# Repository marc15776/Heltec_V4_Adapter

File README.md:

# Heltec LoRa V4 Adapter

This is a fork from [kiu/lofence](https://github.com/kiu/lofence)

I used the the resistor and opamp concept to use  with the [Heltec LoRa V4](https://heltec.org/project/wifi-lora-32-v4/) adc input.
I dont need the microcontroller, LoRa chipset and battery management since that is already integrated on the Heltec V4 board.
I will probably use this in point to point mode with another Heltec board.

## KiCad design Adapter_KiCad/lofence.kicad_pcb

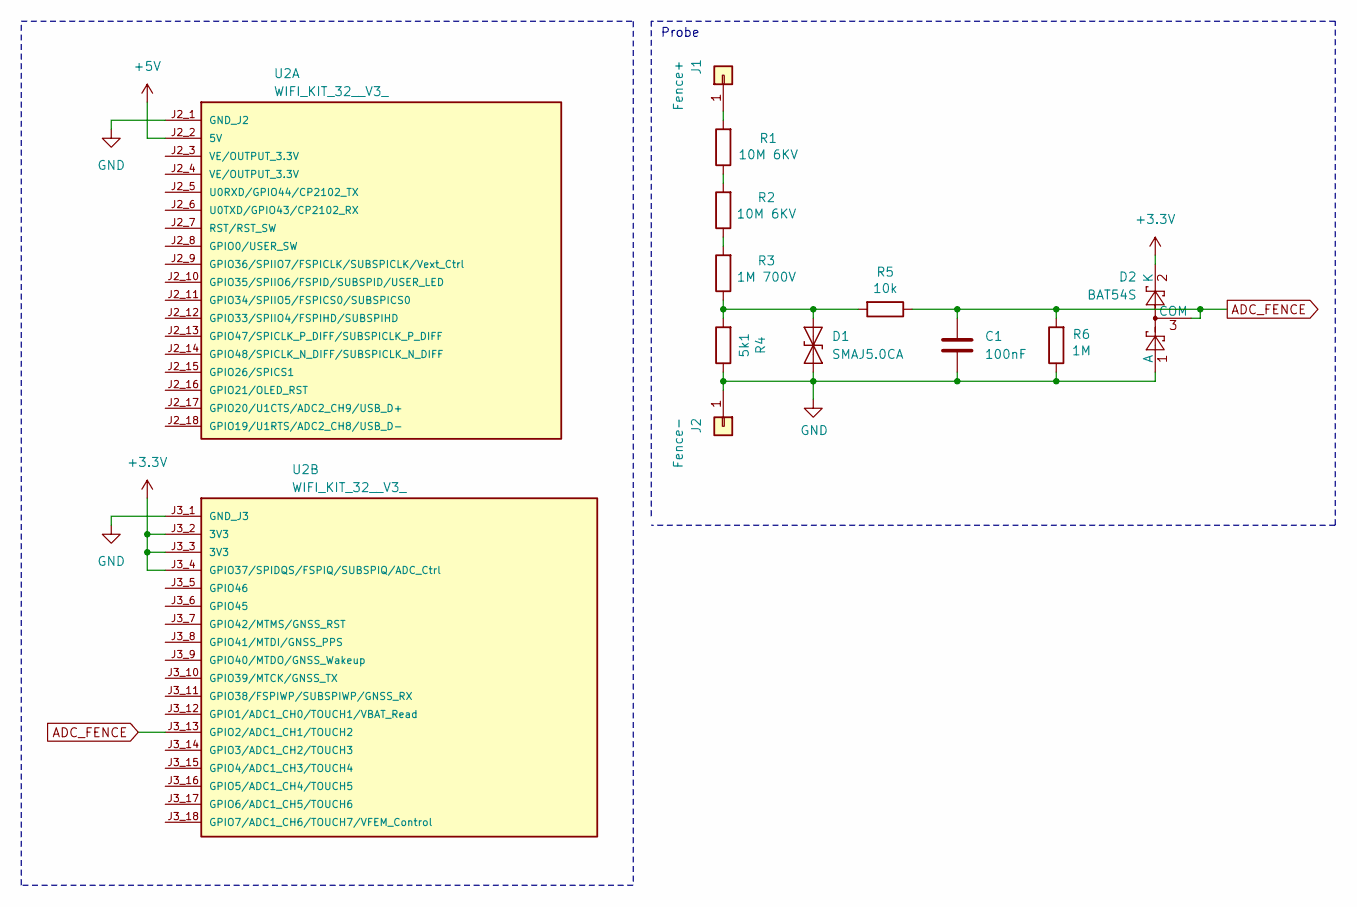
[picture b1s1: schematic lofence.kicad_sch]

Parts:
C1: 100nF; C_0805_2012Metric_Pad1.18x1.45mm_HandSolder
D1: SMAJ5.0CA; D_SMA
D2: BAT54S; SOT-23
J1: Fence+; Measurement_Point_Square-SMD-Pad_Big
J2: Fence-; Measurement_Point_Square-SMD-Pad_Big
R1, R2: 10M 6KV; R_Axial_DIN0414_L11.9mm_D4.5mm_P15.24mm_Horizontal
R3: 1M 700V; R_1206_3216Metric_Pad1.30x1.75mm_HandSolder
R4: 5k1; R_0805_2012Metric_Pad1.20x1.40mm_HandSolder
R5: 10k; R_0805_2012Metric_Pad1.20x1.40mm_HandSolder
R6: 1M; R_0805_2012Metric_Pad1.20x1.40mm_HandSolder
U2: WIFI_KIT_32__V3_; MODULE_WIFI_KIT_32__V3_; PARTREV Rev 1.1

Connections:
+3.3V: D2.2 (K), U2.J3_2 (3V3), U2.J3_3 (3V3), U2.J3_4 (GPIO37/SPIDQS/FSPIQ/SUBSPIQ/ADC_Ctrl)
+5V: U2.J2_2 (5V)
ADC_FENCE: C1.1, D2.3 (COM), R5.1, R6.2, U2.J3_13 (GPIO2/ADC1_CH1/TOUCH2)
GND: C1.2, D1.1 (A1), D2.1 (A), J2.1, R4.1, R6.1, U2.J2_1 (GND_J2), U2.J3_1 (GND_J3)
unnamed: D1.2 (A2), R3.1, R4.2, R5.2
unnamed: J1.1, R1.2
unnamed: R1.1, R2.2
unnamed: R2.1, R3.2

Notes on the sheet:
Probe

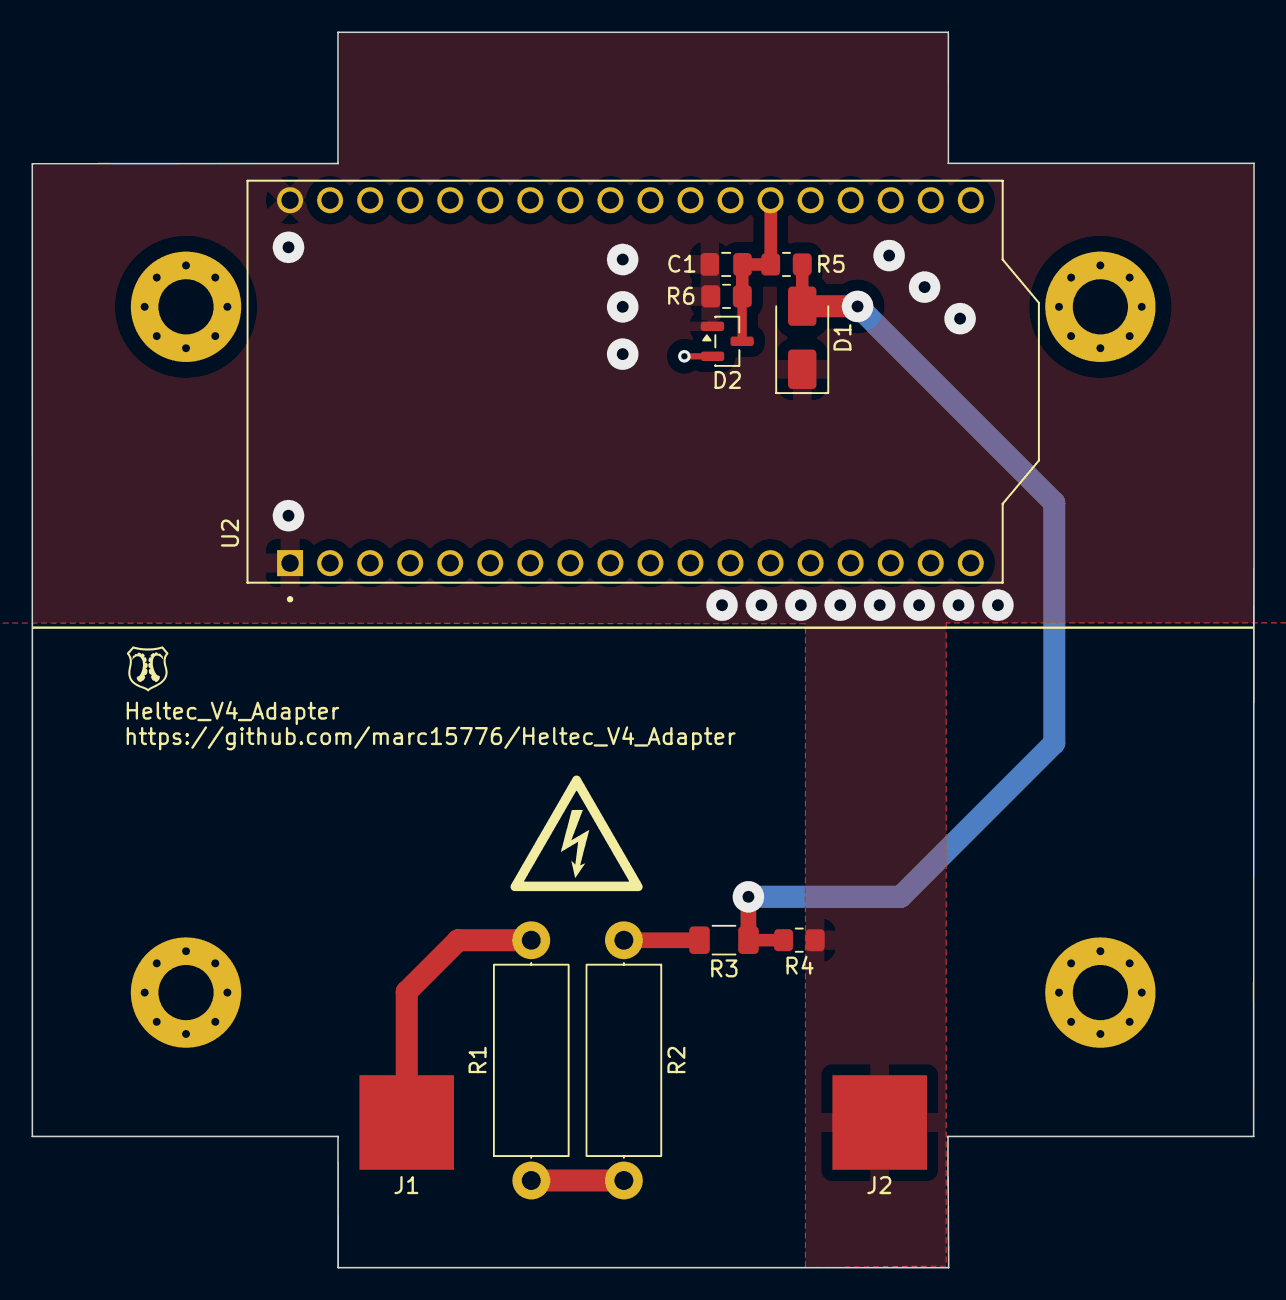
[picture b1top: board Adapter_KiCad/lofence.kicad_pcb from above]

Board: 4 copper layers, 77.5 x 78.4 mm, 12 parts (0 on the bottom side), 7 nets.

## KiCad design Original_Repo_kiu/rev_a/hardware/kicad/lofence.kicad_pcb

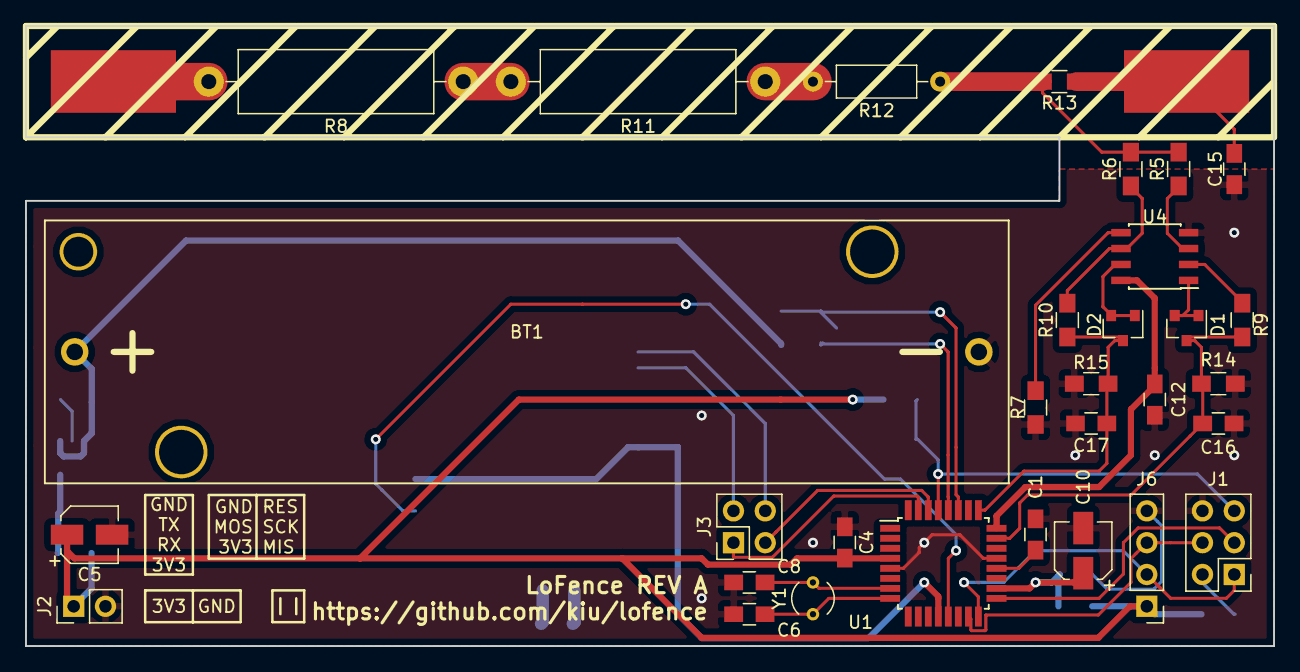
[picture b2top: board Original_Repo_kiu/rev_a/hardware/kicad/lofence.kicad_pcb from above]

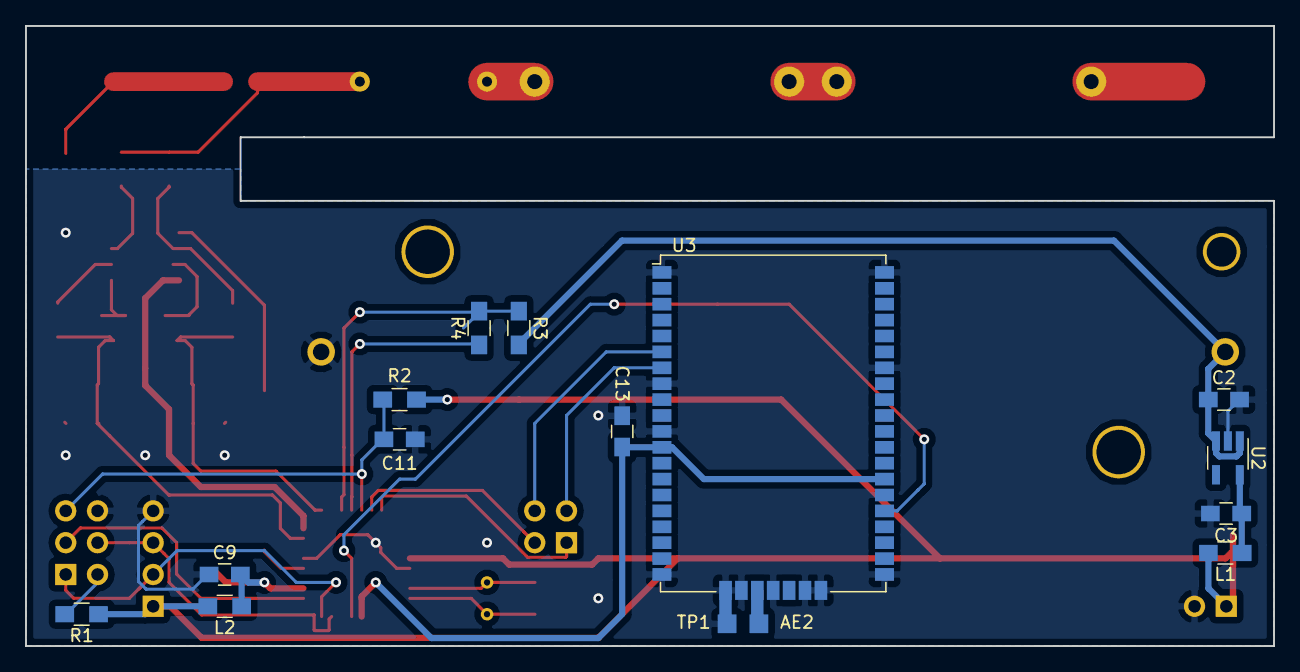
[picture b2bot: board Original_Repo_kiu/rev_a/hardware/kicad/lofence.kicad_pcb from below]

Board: 2 copper layers, 99.7 x 49.5 mm, 48 parts (15 on the bottom side), 36 nets.

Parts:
AE2: Antenna; Measurement_Point_Square-SMD-Pad_Small
BT1: Battery_Cell; 18650HolderTHT
C1, C4, C9, C11, C12, C13, C16, C17: 100nF; C_0805_HandSoldering
C2, C3: 1.0uF; C_0805_HandSoldering
C5, C10: 10uF; CP_Elec_4x5.7
C6, C8: 0pF; C_0805_HandSoldering
C15: 0nF; C_0805_HandSoldering
D1, D2: BAV70LT; SOT-23
J1: ISP; Pin_Header_Straight_2x03_Pitch2.54mm
J2: POWER; Pin_Header_Straight_1x02_Pitch2.54mm
J3: DEBUG RN2483; Pin_Header_Straight_2x02_Pitch2.54mm
J5: Fence+; SolderWirePad_single_SMD_5x10mm
J6: DEBUG RXTX; Pin_Header_Straight_1x04_Pitch2.54mm
J7: Fence-; SolderWirePad_single_SMD_5x10mm
L1: 10uH; R_0805_HandSoldering
L2: Ferrite_Bead; R_0805_HandSoldering
R1: 0R; R_0805_HandSoldering
R2: 4k7; R_0805_HandSoldering
R3, R4: 232R; R_0805_HandSoldering
R5, R6, R7, R9, R10: 100k; R_0805_HandSoldering
R8, R11: 10M 6KV; R_Axial_DIN0516_L15.5mm_D5.0mm_P20.32mm_Horizontal
R12: 1M 700V; R_Axial_DIN0207_L6.3mm_D2.5mm_P10.16mm_Horizontal
R13: 3k9; R_0805_HandSoldering
R14, R15: 1M; R_0805_HandSoldering
TP1: TestPoint; Measurement_Point_Square-SMD-Pad_Small
U1: ATmega328PB-AU; TQFP-32_7x7mm_Pitch0.8mm
U2: MIC5504-3.3YM5; SOT-23-5_HandSoldering
U3: RN2483
U4: Opamp_Dual_Generic; SOIC-8_3.9x4.9mm_Pitch1.27mm
Y1: 32768 Hz; Crystal_AT310_d3.0mm_l10.0mm_Vertical

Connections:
+3.3VADC: C9.2, C10.1, L2.1, U1.18
+3V3: C4.2, C5.1, J2.1, J6.1, L1.2, L2.2, R1.1, R2.1, U1.4
ADC+: C16.1, D1.3, R9.1, R14.2, U1.23
ADC-: C17.1, D2.3, R10.1, R15.2, U1.25
ADC_POWER: C12.2, U1.24, U4.8
BAT_ADC: R3.1, R4.2, U1.27
BAT_GND: R4.1, U1.28
BAT_VCC: BT1.1, C2.1, R3.2, U2.1, U2.3
GND: BT1.2, C1.2, C2.2, C3.2, C4.1, C5.2, C6.1, C8.1, C9.1, C10.2, C11.2, C12.1, C13.1, C15.2, C16.2, C17.2, J1.6, J2.2, J6.4, R7.1, R14.1, R15.1, TP1.1, U1.5, U1.21, U2.2, U3.1, U3.8, U3.11, U3.20, U3.21, U3.22, U3.24, U3.26, U3.27, U3.28, U3.33, U3.41, U3.47, U4.4
MCU_DBG_RX: J1.1, J6.2, U1.16
MCU_DBG_TX: J1.4, J6.3, U1.15
MCU_RESET: C11.1, J1.5, R2.2, U1.29
MCU_RX: J3.3, U1.30
MCU_SCK: J1.3, U1.17
MCU_TX: J3.1, U1.31
unnamed: AE2.1, U3.23
unnamed: C1.1, U1.20
unnamed: C3.1, L1.1, U2.5
unnamed: C6.2, U1.8, Y1.1
unnamed: C8.2, U1.7, Y1.2
unnamed: C15.1, J7.1, R13.1
unnamed: D1.1, D1.2, U4.1
unnamed: D2.1, D2.2, U4.7
unnamed: J1.2, R1.2
unnamed: J5.1, R8.2
unnamed: R5.1, U4.3
unnamed: R7.2, U4.5
unnamed: R9.2, U4.2
unnamed: R6.1, R10.2, U4.6
unnamed: R11.1, R12.2
unnamed: R8.1, R11.2
PROBE: R5.2, R6.2, R12.1, R13.2
RN_POWER: C13.2, U1.12, U3.12, U3.34
RN_RESET: U1.13, U3.32
RN_RX: J3.2, U3.7
RN_TX: J3.4, U3.6

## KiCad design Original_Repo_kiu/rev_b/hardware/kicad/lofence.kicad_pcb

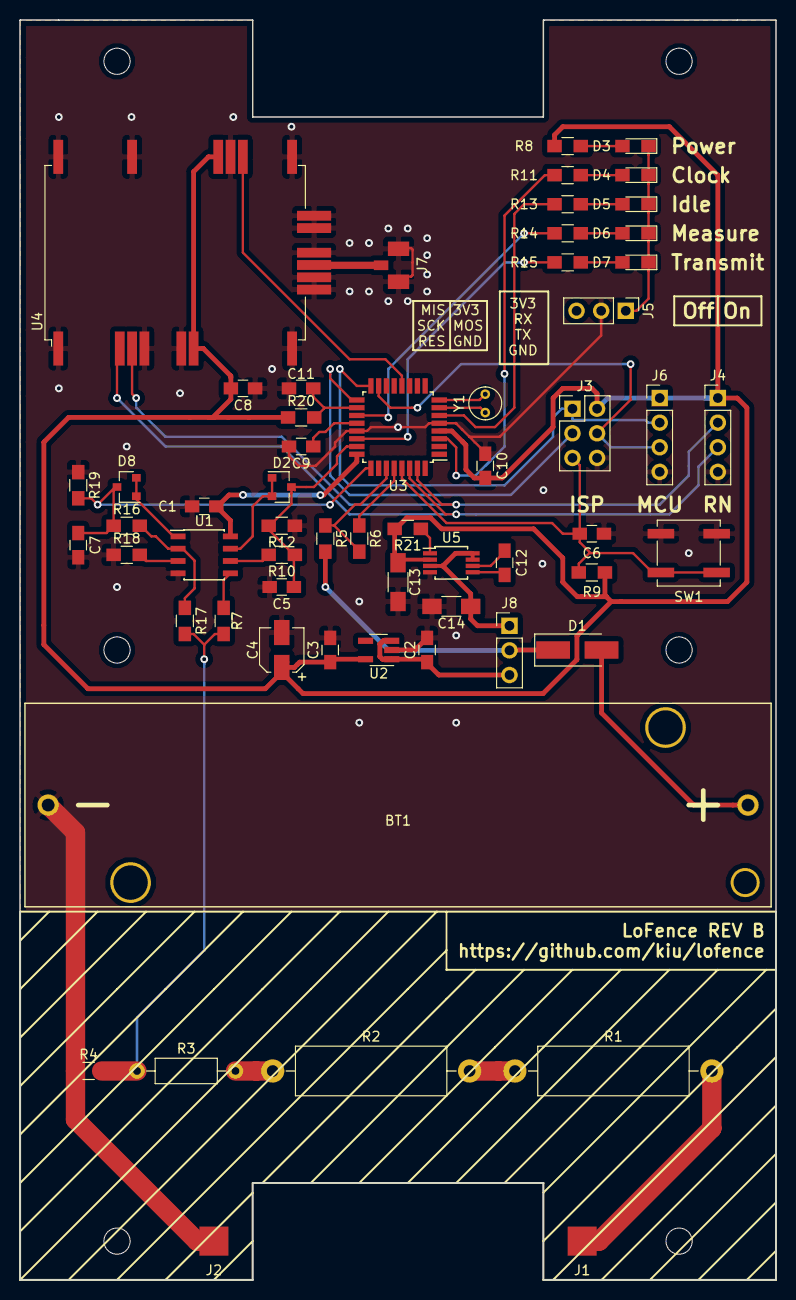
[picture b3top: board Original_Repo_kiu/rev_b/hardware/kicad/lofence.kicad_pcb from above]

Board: 2 copper layers, 78.0 x 130.0 mm, 65 parts (0 on the bottom side), 46 nets.

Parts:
BT1: Battery_Cell; 18650HolderTHT
C1, C5, C6, C7, C8, C9, C10, C11: 100nF; C_0805_HandSoldering
C2, C3: 1.0uF; C_0805_HandSoldering
C4: 10uF; CP_Elec_4x5.7
C12: 1uF; C_0805_HandSoldering
C13, C14: 10uF; C_1206_HandSoldering
D1: D_Schottky; D_SMA_Handsoldering
D2, D8: BAV70LT; SOT-23
D3, D4, D5, D6, D7: LED; LED_0805_HandSoldering
J1: Fence+; Measurement_Point_Square-SMD-Pad_Big
J2: Fence-; Measurement_Point_Square-SMD-Pad_Big
J3: ISP; Pin_Header_Straight_2x03_Pitch2.54mm
J4: DEBUG RN; Pin_Header_Straight_1x04_Pitch2.54mm
J5: DEBUG LED; Pin_Header_Straight_1x03_Pitch2.54mm
J6: DEBUG MCU; Pin_Header_Straight_1x04_Pitch2.54mm
J7: 868; U.FL
J8: PWR; Pin_Header_Straight_1x03_Pitch2.54mm
MH1, MH2, MH3, MH4, MH5, MH6: MountingHole; MountingHole_2.7mm_M2.5
R1, R2: 10M 6KV; R_Axial_DIN0516_L15.5mm_D5.0mm_P20.32mm_Horizontal
R3: 1M 700V; R_Axial_DIN0207_L6.3mm_D2.5mm_P10.16mm_Horizontal
R4: 3k9; R_0805_HandSoldering
R5, R6: 232R; R_0805_HandSoldering
R7, R10, R16, R17, R18, R21: 100k; R_0805_HandSoldering
R8, R11, R13, R14, R15: R; R_0805_HandSoldering
R9: 4k7; R_0805_HandSoldering
R12, R19: 1M; R_0805_HandSoldering
R20: 47R; R_0805_HandSoldering
SW1: RESET; SW_SPST_B3SL-1002P
U1: Opamp_Dual_Generic; SOIC-8_3.9x4.9mm_Pitch1.27mm
U2: MIC5504-3.3YM5; SOT-23-5_HandSoldering
U3: ATmega328PB-AU; TQFP-32_7x7mm_Pitch0.8mm
U4: RN2483; RN2483_serial
U5: MCP125x; MSOP-8_3x3mm_Pitch0.65mm
Y1: 32768 Hz; Crystal_Round_d3.0mm_Vertical

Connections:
+3V3: C3.1, C4.1, C8.2, C10.2, C13.1, J3.2, J4.1, J6.1, R8.2, R9.1, R20.1, R21.2, U2.5, U3.4, U4.12, U4.34, U5.2
ADC+: C5.1, D2.3, R10.1, R12.2, U3.23
ADC-: C7.1, D8.3, R16.1, R19.2, U3.25
ADC_POWER: C1.1, U1.8, U3.24
AVCC: C11.2, R20.2, U3.18
BAT_ADC: R5.1, R6.2, U3.27
BAT_GND: R6.1, U3.28
BAT_VCC: D1.1, J8.2, R5.2
GND: BT1.2, C1.2, C2.2, C3.2, C4.2, C5.2, C6.2, C7.2, C8.1, C9.2, C10.1, C11.1, C13.2, C14.2, J2.1, J3.6, J4.4, J5.2, J6.4, J7.2, R4.1, R12.1, R18.1, R19.1, SW1.2, U1.4, U2.2, U3.5, U3.21, U4.1, U4.8, U4.11, U4.20, U4.21, U4.22, U4.24, U4.26, U4.27, U4.28, U4.33, U4.41, U4.47, U5.4
LED_CLK: R11.2, U3.3
LED_IDLE: R13.2, U3.6
LED_MSR: R14.2, U3.19
LED_TX: R15.2, U3.22
MCU_MISO: J3.1, J6.2, U3.16
MCU_MOSI: J3.4, J6.3, U3.15
MCU_RESET: C6.1, J3.5, R9.2, SW1.1, U3.29
MCU_SCK: J3.3, U3.17
unnamed: BT1.1, D1.2
unnamed: C9.1, U3.20
unnamed: C12.1, U5.6
unnamed: C12.2, U5.5
unnamed: D2.1, D2.2, U1.7
unnamed: D3.1, D4.1, D5.1, D6.1, D7.1, J5.1
unnamed: D3.2, R8.1
unnamed: D4.2, R11.1
unnamed: D5.2, R13.1
unnamed: D6.2, R14.1
unnamed: D7.2, R15.1
unnamed: D8.1, D8.2, U1.1
unnamed: J1.1, R1.2
unnamed: J7.1, U4.23
unnamed: R1.1, R2.2
unnamed: R2.1, R3.2
unnamed: R7.1, U1.5
unnamed: R10.2, U1.6
unnamed: R16.2, R17.1, U1.2
unnamed: R18.2, U1.3
unnamed: R21.1, U5.1
unnamed: U3.7, Y1.1
unnamed: U3.8, Y1.2
PROBE: R3.1, R4.2, R7.2, R17.2
RN_RESET: U3.12, U4.32
RN_RX: J4.2, U3.31, U4.7
RN_TX: J4.3, U3.30, U4.6
VCC_BBC: C14.1, J8.1, U5.3, U5.7, U5.8
VCC_LDO: C2.1, J8.3, U2.1, U2.3

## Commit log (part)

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2026-03-21 First update
2026-03-21 First changes in KiCad
2026-03-21 Finished PCB & Schematic
2026-03-21 Added BOM for PCB
2026-03-26 Minor changes to pcb
2026-03-26 Added Gerber files
2026-04-11 PlatformIO Setup
2026-04-13 First working code
2026-04-16 Halfway working code
2026-06-24 Funktionierende Home Node ohne LoRa
